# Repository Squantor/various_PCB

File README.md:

Various prototype PCB's
===========
This repository contains various little boards like level shifters, component breakouts and other simple PCB's. Most of these boards are breadboard plugin friendly and are available at OSH park.
<h1 align="center">Breakouts</h1>
Various breakout boards with additional supporting components to help the application
<h2 align="center">74HCT9046A PLL</h2>
Improved version of the venerable 47HC(T)4046 PLL, main improvement is fixing the deadtime problem with the Flipflop based phase detector and adding a bias resistor for the charge pump output.
<h2 align="center">GTL2003 level shifter</h2>
Bidirectional levelshifter working from 5V on one side to anything lower on the other. Pull up and biasing resistor pads/caps positions included.
<h2 align="center">GTL2003 current mirror/sink</h2>
The GTL2003 bidirectional levelshifter is nothing more then a bunch of N-MOSFETs on a single die with their gates interconnected. Due to close proximity of the FETs to eachother they (should) be reasonably matched well and the datasheet specifies this. Instead of using it for a level shifter application it could also be a multiple channel programmable current sink. Included on the board is a TL431 programmable zener reference with a bunch of resistor pads for biasing the mosfets with a stable voltage.
<h2 align="center">Filament transformer breakout</h2>
Breakout board for the Triad transformer 6.3V, used as a filament transformer for electrostatic CRT's. Going to be used for PM3210 oscilloscope repair.
<h1 align="center">Modules</h1>
<h2 align="center">Transformer module</h2>
Board with flexible transformer layout, bridge rectifier and smoothing caps. Multiple versions.

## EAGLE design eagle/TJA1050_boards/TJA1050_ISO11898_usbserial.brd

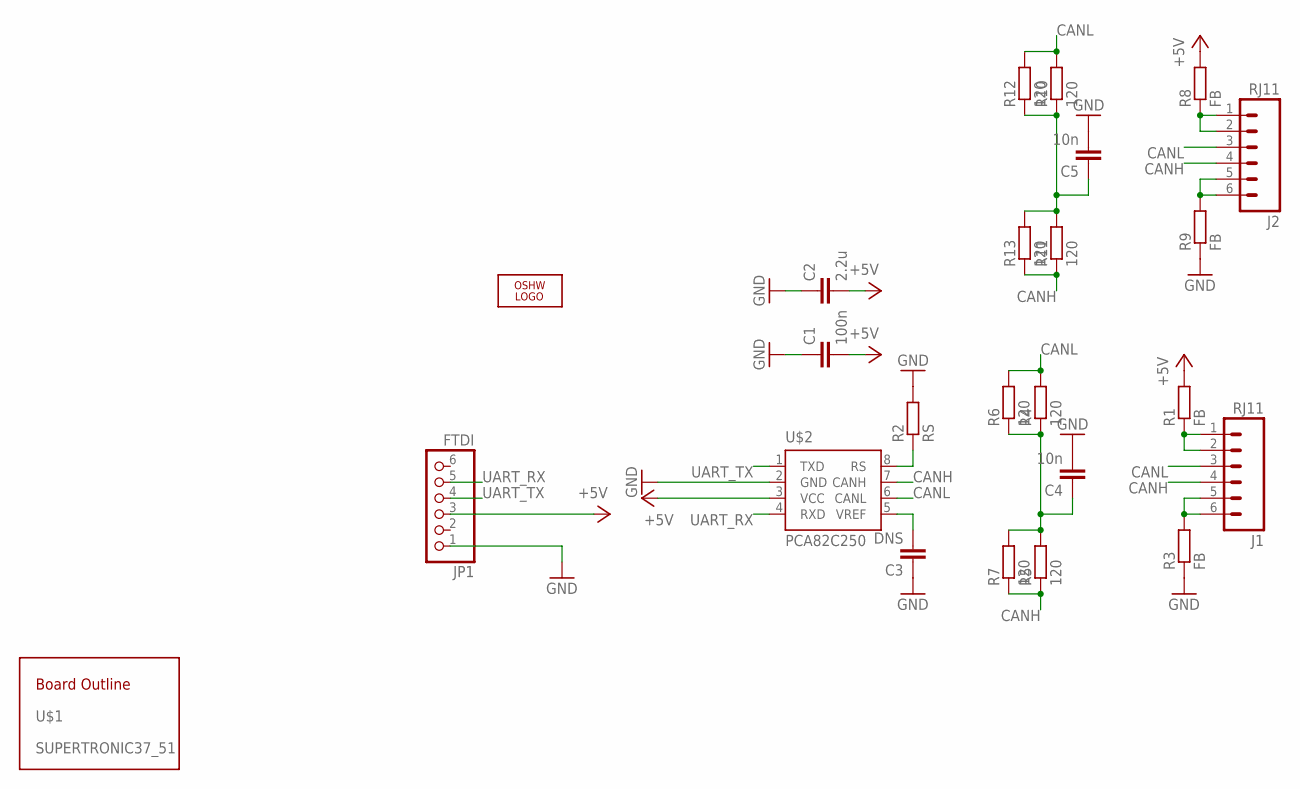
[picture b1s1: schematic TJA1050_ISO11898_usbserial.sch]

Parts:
C1: 100n; C0603
C2: 2.2u; C0805
C3: DNS; C0603
C4, C5: 10n; C0805
J1, J2: RJ11; RJ11-6
JP1: FTDI; 1X06
LOGO1: OSHW_LOGO_10MILX0200-NT; OSHW_10X200_NOTEXT
R1, R3, R8, R9: FB; R0805
R2: RS; R0603
R4, R5, R6, R7, R10, R11, R12, R13: 120; R0603
U$1: SUPERTRONIC37_51; SUPERTRONIC_37_51MM
U$2: PCA82C250; SOT96-1

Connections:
+5V: C1.2, C2.2, JP1.3, R1.2, R8.2, U$2.3 (VCC)
CANH: J1.4, J2.4, R5.1, R7.1, R11.1, R13.1, U$2.7 (CANH)
CANL: J1.3, J2.3, R4.2, R6.2, R10.2, R12.2, U$2.6 (CANL)
GND: C1.1, C2.1, C3.1, C4.2, C5.2, JP1.1, R2.2, R3.1, R9.1, U$2.2 (GND)
unnamed: J1.1, J1.2, R1.1
unnamed: C3.2, U$2.5 (VREF)
unnamed: J1.5, J1.6, R3.2
unnamed: C4.1, R4.1, R5.2, R6.1, R7.2
unnamed: R2.1, U$2.8 (RS)
unnamed: J2.1, J2.2, R8.1
unnamed: J2.5, J2.6, R9.2
unnamed: C5.1, R10.1, R11.2, R12.1, R13.2
UART_RX: JP1.5, U$2.4 (RXD)
UART_TX: JP1.4, U$2.1 (TXD)

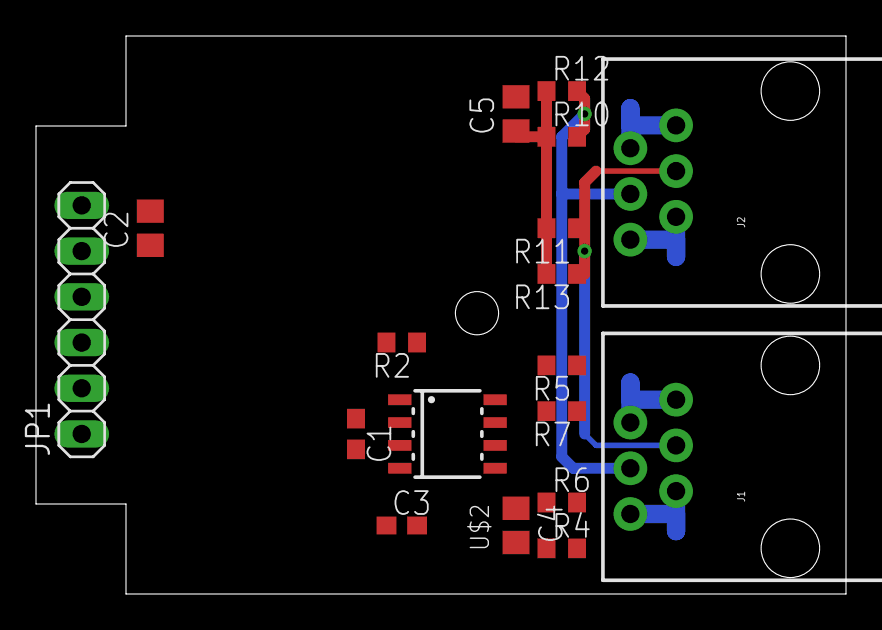
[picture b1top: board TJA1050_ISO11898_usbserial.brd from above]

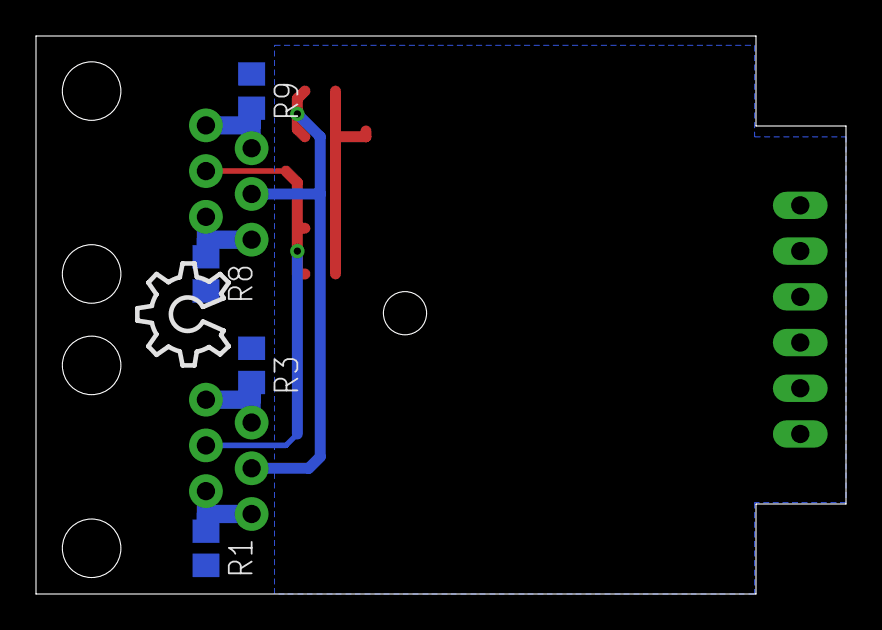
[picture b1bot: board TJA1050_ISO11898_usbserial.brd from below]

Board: 2 copper layers, 45.0 x 31.0 mm, 24 parts (5 on the bottom side), 14 nets.

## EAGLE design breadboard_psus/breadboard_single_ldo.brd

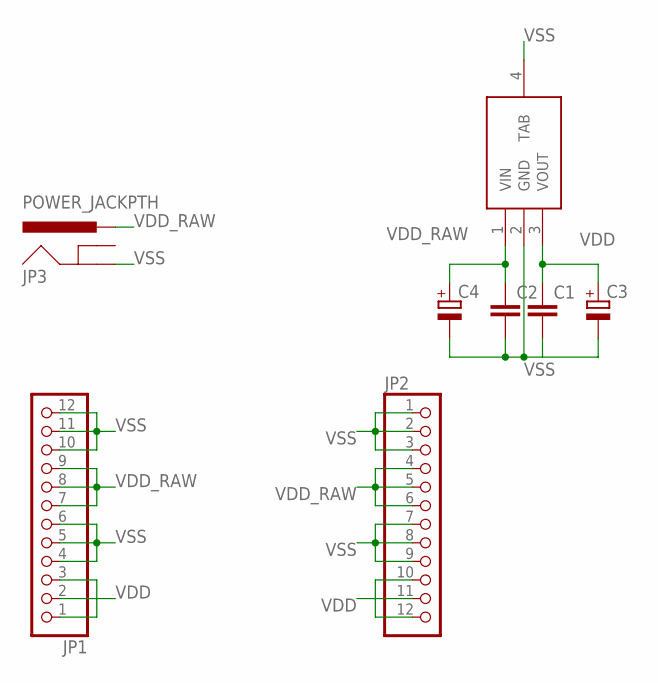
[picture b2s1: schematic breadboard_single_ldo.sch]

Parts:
C1, C2: C-EUC0805; C0805
C3, C4: CPOL-EUE3.5-8; E3,5-8
JP1, JP2: PINHD-1X12NORM_OCT; 1X12_NORMAL_OCT
JP3: POWER_JACKPTH; POWER_JACK_PTH
U$1: MCP1703T-3302E/DB; SOT223

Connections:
VDD: C1.1, C3.+, JP1.1, JP1.2, JP1.3, JP2.10, JP2.11, JP2.12, U$1.3 (VOUT)
VDD_RAW: C2.1, C4.+, JP1.7, JP1.8, JP1.9, JP2.4, JP2.5, JP2.6, JP3.PWR, U$1.1 (VIN)
VSS: C1.2, C2.2, C3.-, C4.-, JP1.4, JP1.5, JP1.6, JP1.10, JP1.11, JP1.12, JP2.1, JP2.2, JP2.3, JP2.7, JP2.8, JP2.9, JP3.GND, U$1.2 (GND), U$1.4 (TAB)

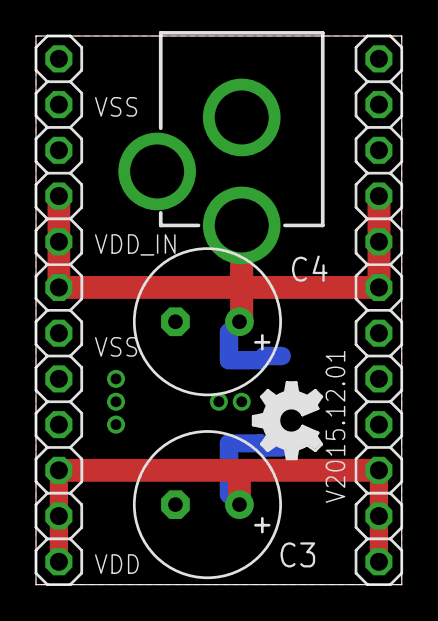
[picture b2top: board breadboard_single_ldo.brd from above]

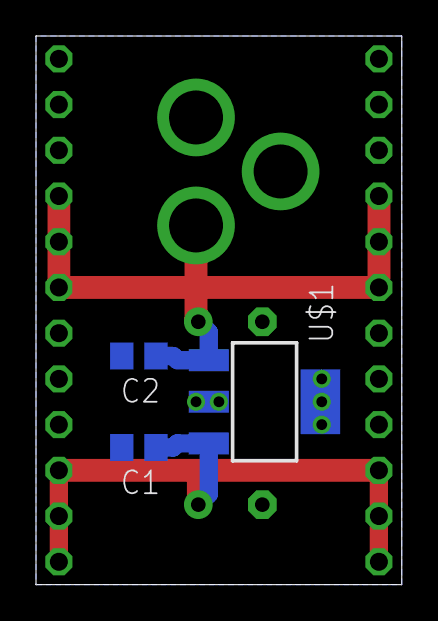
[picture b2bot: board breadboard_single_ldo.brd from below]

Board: 2 copper layers, 20.3 x 30.5 mm, 9 parts (3 on the bottom side), 3 nets.

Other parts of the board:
LOGO1: OSHW_LOGO_FILLX0150-NT; OSHW_FILLX150_NOTEXT

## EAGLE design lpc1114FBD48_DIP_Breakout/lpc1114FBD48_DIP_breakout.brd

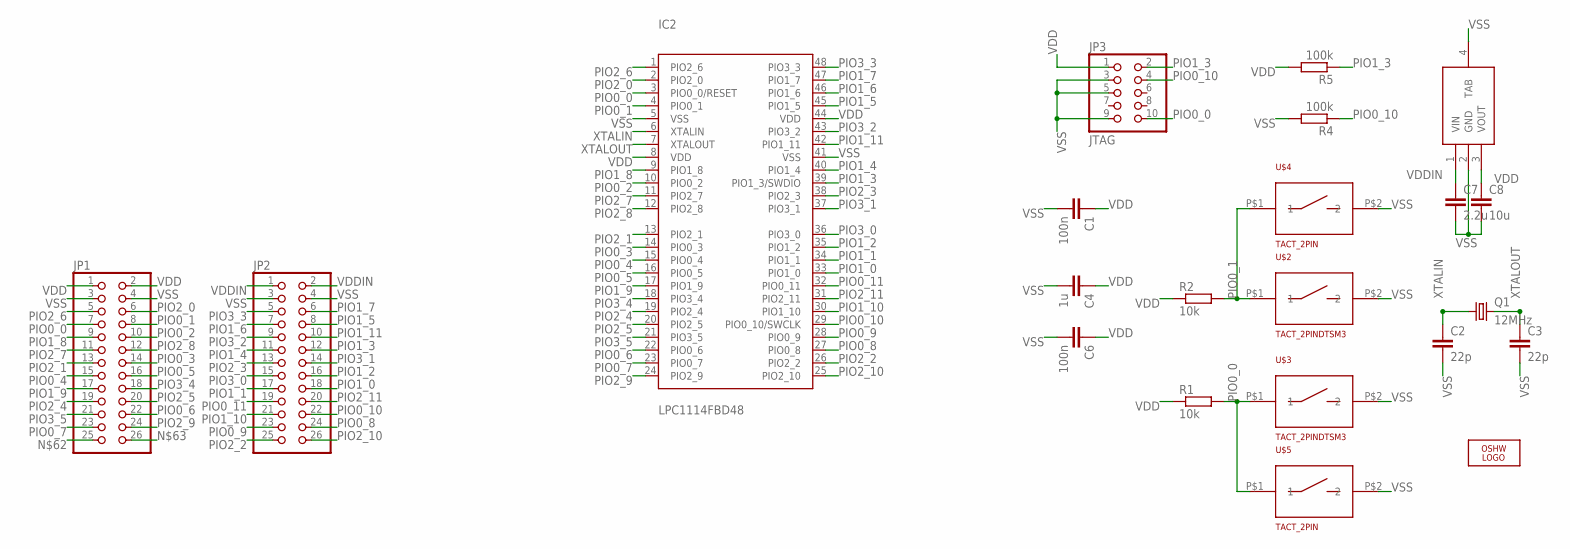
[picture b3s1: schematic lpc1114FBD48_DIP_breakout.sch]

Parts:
C1, C6: 100n; C0603K
C2, C3: 22p; C0603K
C4: 1u; C0805K
C7: 2.2u; C0805
C8: 10u; C0805
IC1: MCP1703T-3302E/DB; SOT223
IC2: LPC1114FBD48; SOT313-2
JP1, JP2: PINHD-2X13; 2X13
JP3: JTAG; 2X05_1.27_SMD
LOGO2: OSHW_LOGO_FILLX0150-NT; OSHW_FILLX150_NOTEXT
Q1: 12MHz; CRYSTAL_5.0X3.2
R1, R2: 10k; R0603
R4, R5: 100k; R0603
U$2, U$3: TACT_2PINDTSM3; DTSM3
U$4, U$5: TACT_2PIN; TD-85XU

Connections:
PIO0_0: IC2.3 (PIO0_0/RESET), JP1.7, JP3.10, R1.2, U$3.P$1 (1), U$5.P$1 (1)
PIO0_1: IC2.4 (PIO0_1), JP1.8, R2.2, U$2.P$1 (1), U$4.P$1 (1)
PIO0_2: IC2.10 (PIO0_2), JP1.10
PIO0_3: IC2.14 (PIO0_3), JP1.14
PIO0_4: IC2.15 (PIO0_4), JP1.15
PIO0_5: IC2.16 (PIO0_5), JP1.16
PIO0_6: IC2.22 (PIO0_6), JP1.22
PIO0_7: IC2.23 (PIO0_7), JP1.23
PIO0_8: IC2.27 (PIO0_8), JP2.24
PIO0_9: IC2.28 (PIO0_9), JP2.23
PIO0_10: IC2.29 (PIO0_10/SWCLK), JP2.22, JP3.4, R4.1
PIO0_11: IC2.32 (PIO0_11), JP2.19
PIO1_0: IC2.33 (PIO1_0), JP2.18
PIO1_1: IC2.34 (PIO1_1), JP2.17
PIO1_2: IC2.35 (PIO1_2), JP2.16
PIO1_3: IC2.39 (PIO1_3/SWDIO), JP2.12, JP3.2, R5.1
PIO1_4: IC2.40 (PIO1_4), JP2.11
PIO1_5: IC2.45 (PIO1_5), JP2.8
PIO1_6: IC2.46 (PIO1_6), JP2.7
PIO1_7: IC2.47 (PIO1_7), JP2.6
PIO1_8: IC2.9 (PIO1_8), JP1.9
PIO1_9: IC2.17 (PIO1_9), JP1.17
PIO1_10: IC2.30 (PIO1_10), JP2.21
PIO1_11: IC2.42 (PIO1_11), JP2.10
PIO2_0: IC2.2 (PIO2_0), JP1.6
PIO2_1: IC2.13 (PIO2_1), JP1.13
PIO2_2: IC2.26 (PIO2_2), JP2.25
PIO2_3: IC2.38 (PIO2_3), JP2.13
PIO2_4: IC2.19 (PIO2_4), JP1.19
PIO2_5: IC2.20 (PIO2_5), JP1.20
PIO2_6: IC2.1 (PIO2_6), JP1.5
PIO2_7: IC2.11 (PIO2_7), JP1.11
PIO2_8: IC2.12 (PIO2_8), JP1.12
PIO2_9: IC2.24 (PIO2_9), JP1.24
PIO2_10: IC2.25 (PIO2_10), JP2.26
PIO2_11: IC2.31 (PIO2_11), JP2.20
PIO3_0: IC2.36 (PIO3_0), JP2.15
PIO3_1: IC2.37 (PIO3_1), JP2.14
PIO3_2: IC2.43 (PIO3_2), JP2.9
PIO3_3: IC2.48 (PIO3_3), JP2.5
PIO3_4: IC2.18 (PIO3_4), JP1.18
PIO3_5: IC2.21 (PIO3_5), JP1.21
VDD: C1.1, C4.1, C6.1, C8.1, IC1.3 (VOUT), IC2.8 (VDD), IC2.44 (VDD), JP1.1, JP1.2, JP3.1, R1.1, R2.1, R5.2
VDDIN: C7.1, IC1.1 (VIN), JP2.1, JP2.2
VSS: C1.2, C2.2, C3.2, C4.2, C6.2, C7.2, C8.2, IC1.2 (GND), IC1.4 (TAB), IC2.5 (VSS), IC2.41 (VSS), JP1.3, JP1.4, JP2.3, JP2.4, JP3.3, JP3.5, JP3.9, R4.2, U$2.P$2 (2), U$3.P$2 (2), U$4.P$2 (2), U$5.P$2 (2)
XTALIN: C2.1, IC2.6 (XTALIN), Q1.1
XTALOUT: C3.1, IC2.7 (XTALOUT), Q1.2

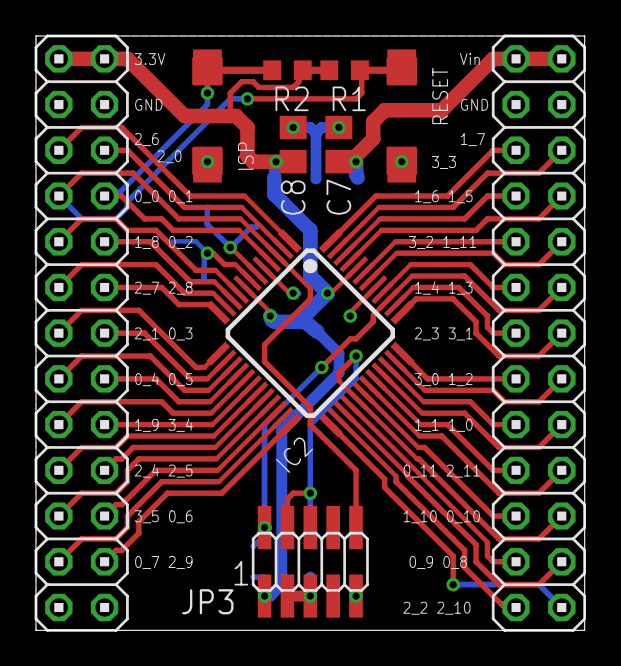
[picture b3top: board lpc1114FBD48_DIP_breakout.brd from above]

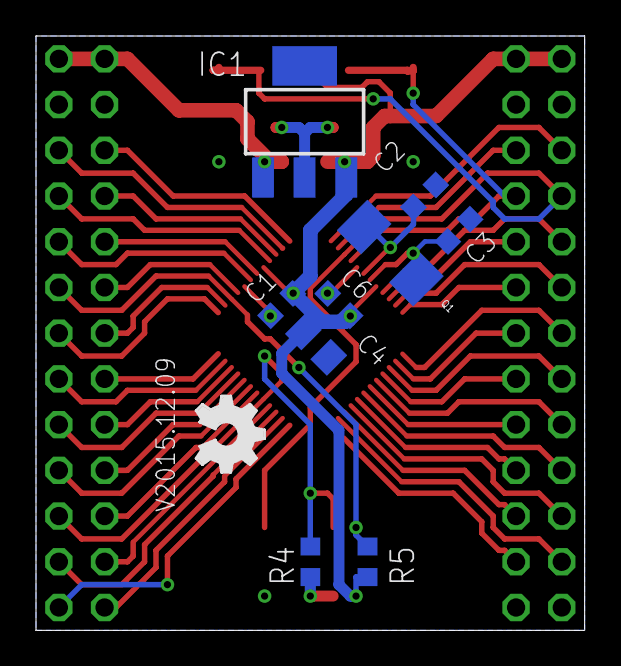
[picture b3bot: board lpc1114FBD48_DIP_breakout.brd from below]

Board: 2 copper layers, 30.5 x 33.0 mm, 22 parts (10 on the bottom side), 47 nets.

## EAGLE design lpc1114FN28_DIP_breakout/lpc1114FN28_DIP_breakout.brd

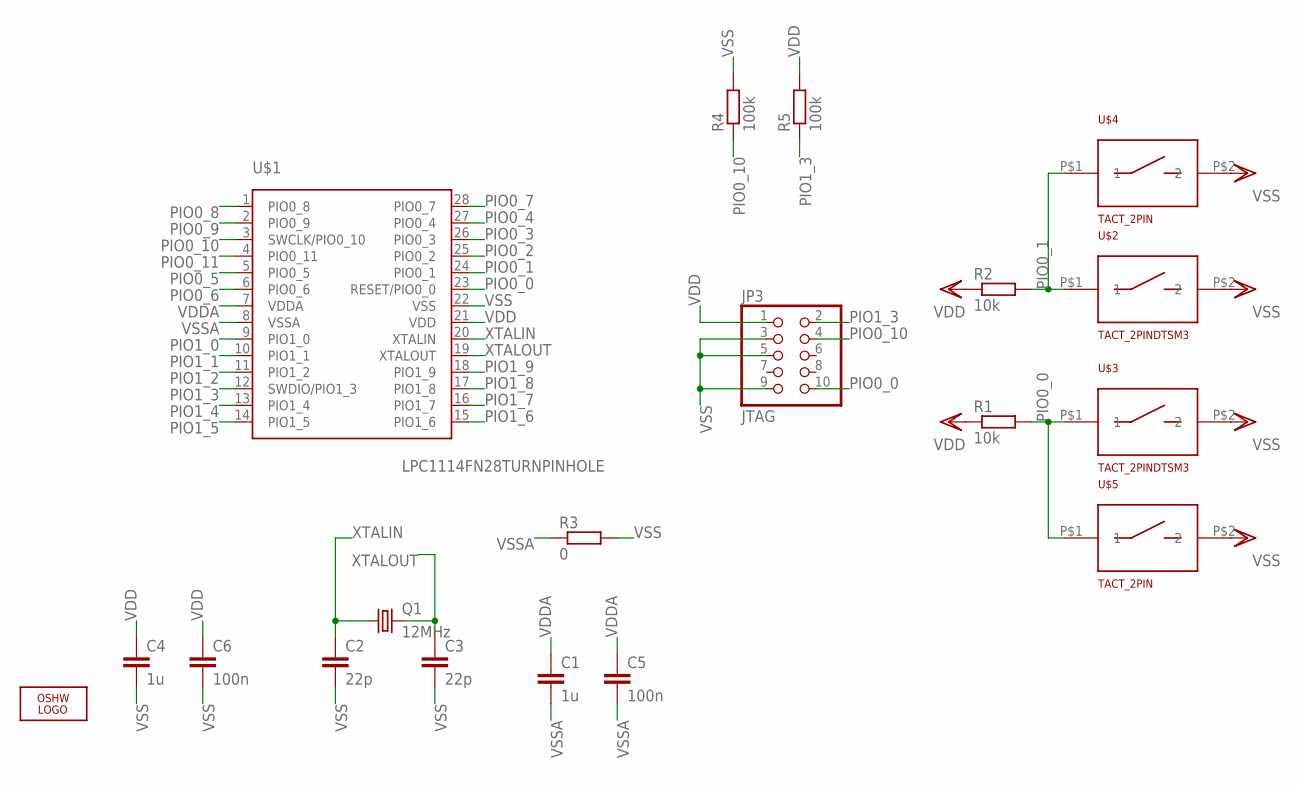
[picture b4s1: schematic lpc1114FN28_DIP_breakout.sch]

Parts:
C1, C4: 1u; C0805K
C2, C3: 22p; C0603K
C5, C6: 100n; C0603K
JP3: JTAG; 2X05_1.27_SMD
LOGO2: OSHW_LOGO_FILLX0150-NT; OSHW_FILLX150_NOTEXT
Q1: 12MHz; CRYSTAL_5.0X3.2
R1, R2: 10k; R0603
R3: 0; R0603
R4, R5: 100k; R0603
U$1: LPC1114FN28TURNPINHOLE; SOT117_TURNPINHOLE
U$2, U$3: TACT_2PINDTSM3; DTSM3
U$4, U$5: TACT_2PIN; TD-85XU

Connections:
PIO0_0: JP3.10, R1.2, U$1.23 (RESET/PIO0_0), U$3.P$1 (1), U$5.P$1 (1)
PIO0_1: R2.2, U$1.24 (PIO0_1), U$2.P$1 (1), U$4.P$1 (1)
PIO0_2: U$1.25 (PIO0_2)
PIO0_3: U$1.26 (PIO0_3)
PIO0_4: U$1.27 (PIO0_4)
PIO0_5: U$1.5 (PIO0_5)
PIO0_6: U$1.6 (PIO0_6)
PIO0_7: U$1.28 (PIO0_7)
PIO0_8: U$1.1 (PIO0_8)
PIO0_9: U$1.2 (PIO0_9)
PIO0_10: JP3.4, R4.1, U$1.3 (SWCLK/PIO0_10)
PIO0_11: U$1.4 (PIO0_11)
PIO1_0: U$1.9 (PIO1_0)
PIO1_1: U$1.10 (PIO1_1)
PIO1_2: U$1.11 (PIO1_2)
PIO1_3: JP3.2, R5.1, U$1.12 (SWDIO/PIO1_3)
PIO1_4: U$1.13 (PIO1_4)
PIO1_5: U$1.14 (PIO1_5)
PIO1_6: U$1.15 (PIO1_6)
PIO1_7: U$1.16 (PIO1_7)
PIO1_8: U$1.17 (PIO1_8)
PIO1_9: U$1.18 (PIO1_9)
VDD: C4.1, C6.1, JP3.1, R1.1, R2.1, R5.2, U$1.21 (VDD)
VDDA: C1.1, C5.1, U$1.7 (VDDA)
VSS: C2.2, C3.2, C4.2, C6.2, JP3.3, JP3.5, JP3.9, R3.2, R4.2, U$1.22 (VSS), U$2.P$2 (2), U$3.P$2 (2), U$4.P$2 (2), U$5.P$2 (2)
VSSA: C1.2, C5.2, R3.1, U$1.8 (VSSA)
XTALIN: C2.1, Q1.1, U$1.20 (XTALIN)
XTALOUT: C3.1, Q1.2, U$1.19 (XTALOUT)

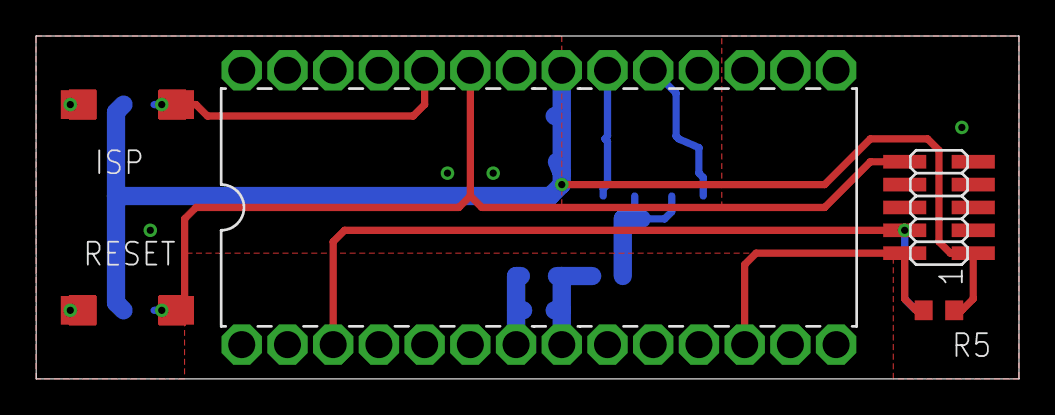
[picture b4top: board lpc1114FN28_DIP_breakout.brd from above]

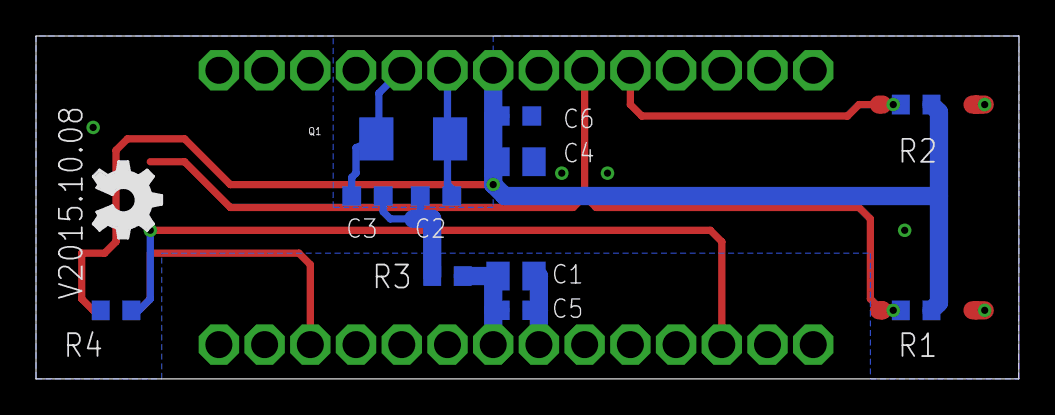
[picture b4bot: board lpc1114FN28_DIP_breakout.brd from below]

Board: 2 copper layers, 54.6 x 19.1 mm, 19 parts (12 on the bottom side), 10 nets.

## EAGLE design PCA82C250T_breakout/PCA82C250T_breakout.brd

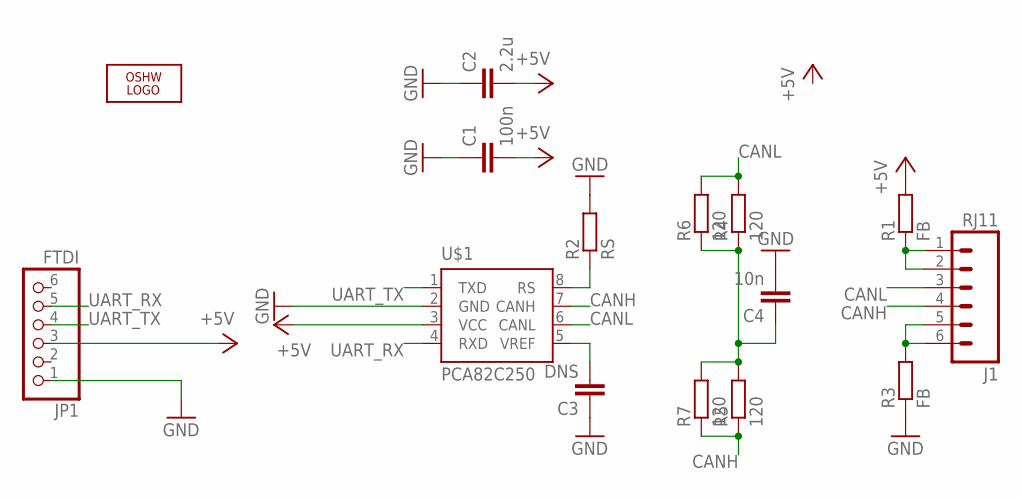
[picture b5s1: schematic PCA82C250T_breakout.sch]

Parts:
C1: 100n; C0603
C2: 2.2u; C0805
C3: DNS; C0603
C4: 10n; C0805
J1: RJ11; RJ11-6
JP1: FTDI; 1X06
LOGO1: OSHW_LOGO_10MILX0200-NT; OSHW_10X200_NOTEXT
R1, R3: FB; R0805
R2: RS; R0603
R4, R5, R6, R7: 120; R0603
U$1: PCA82C250; SOT96-1

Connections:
+5V: C1.2, C2.2, JP1.3, R1.2, U$1.3 (VCC)
CANH: J1.4, R5.1, R7.1, U$1.7 (CANH)
CANL: J1.3, R4.2, R6.2, U$1.6 (CANL)
GND: C1.1, C2.1, C3.1, C4.2, JP1.1, R2.2, R3.1, U$1.2 (GND)
unnamed: J1.1, J1.2, R1.1
unnamed: C3.2, U$1.5 (VREF)
unnamed: J1.5, J1.6, R3.2
unnamed: C4.1, R4.1, R5.2, R6.1, R7.2
unnamed: R2.1, U$1.8 (RS)
UART_RX: JP1.5, U$1.4 (RXD)
UART_TX: JP1.4, U$1.1 (TXD)

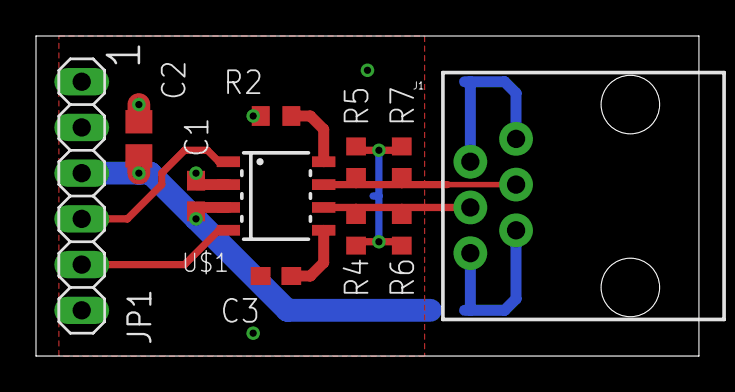
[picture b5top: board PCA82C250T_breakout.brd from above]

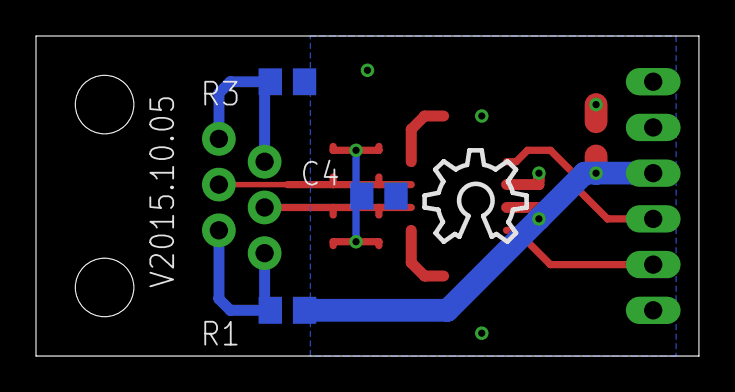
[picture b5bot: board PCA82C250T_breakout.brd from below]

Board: 2 copper layers, 36.8 x 17.8 mm, 15 parts (4 on the bottom side), 11 nets.

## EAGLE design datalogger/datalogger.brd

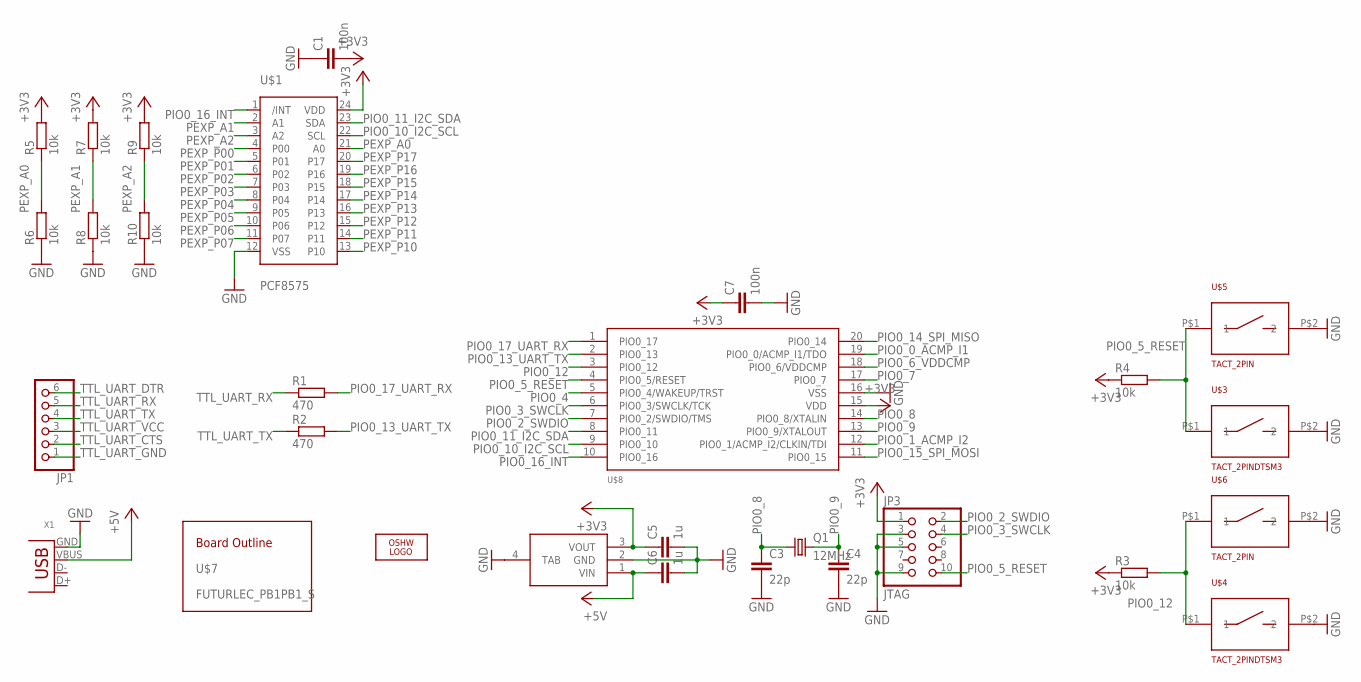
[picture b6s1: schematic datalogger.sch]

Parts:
C1, C7: 100n; C0603K
C3, C4: 22p; C0603K
C5, C6: 1u; C0805K
JP1: PINHD-1X6; 1X06
JP3: JTAG; 2X05_1.27_SMD
LOGO2: OSHW_LOGO_FILLX0150-NT; OSHW_FILLX150_NOTEXT
Q1: 12MHz; CRYSTAL_5.0X3.2
R1, R2: 470; R0603
R3, R4, R5, R6, R7, R8, R9, R10: 10k; R0603
U$1: PCF8575; SOT340
U$2: MCP1703T-3302E/DB; SOT223
U$3, U$4: TACT_2PINDTSM3; DTSM3
U$5, U$6: TACT_2PIN; TD-85XU
U$7: FUTURLEC_PB1PB1_S; FUTURLEC_PB1_SMALL
U$8: LPC812M101JDH20; TSSOP20
X1: USB-B-H

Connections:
+3V3: C1.2, C5.1, C7.1, JP3.1, R3.1, R4.1, R5.2, R7.2, R9.2, U$1.24 (VDD), U$2.3 (VOUT), U$8.15 (VDD)
+5V: C6.1, U$2.1 (VIN), X1.VBUS
GND: C1.1, C3.2, C4.2, C5.2, C6.2, C7.2, JP3.3, JP3.5, JP3.9, R6.1, R8.1, R10.1, U$1.12 (VSS), U$2.2 (GND), U$2.4 (TAB), U$3.P$2 (2), U$4.P$2 (2), U$5.P$2 (2), U$6.P$2 (2), U$8.16 (VSS), X1.GND
PEXP_A0: R5.1, R6.2, U$1.21 (A0)
PEXP_A1: R7.1, R8.2, U$1.2 (A1)
PEXP_A2: R9.1, R10.2, U$1.3 (A2)
PEXP_P00: U$1.4 (P00)
PEXP_P01: U$1.5 (P01)
PEXP_P02: U$1.6 (P02)
PEXP_P03: U$1.7 (P03)
PEXP_P04: U$1.8 (P04)
PEXP_P05: U$1.9 (P05)
PEXP_P06: U$1.10 (P06)
PEXP_P07: U$1.11 (P07)
PEXP_P10: U$1.13 (P10)
PEXP_P11: U$1.14 (P11)
PEXP_P12: U$1.15 (P12)
PEXP_P13: U$1.16 (P13)
PEXP_P14: U$1.17 (P14)
PEXP_P15: U$1.18 (P15)
PEXP_P16: U$1.19 (P16)
PEXP_P17: U$1.20 (P17)
PIO0_0_ACMP_I1: U$8.19 (PIO0_0/ACMP_I1/TDO)
PIO0_1_ACMP_I2: U$8.12 (PIO0_1/ACMP_I2/CLKIN/TDI)
PIO0_2_SWDIO: JP3.2, U$8.7 (PIO0_2/SWDIO/TMS)
PIO0_3_SWCLK: JP3.4, U$8.6 (PIO0_3/SWCLK/TCK)
PIO0_4: U$8.5 (PIO0_4/WAKEUP/TRST)
PIO0_5_RESET: JP3.10, R4.2, U$3.P$1 (1), U$5.P$1 (1), U$8.4 (PIO0_5/RESET)
PIO0_6_VDDCMP: U$8.18 (PIO0_6/VDDCMP)
PIO0_7: U$8.17 (PIO0_7)
PIO0_8: C3.1, Q1.1, U$8.14 (PIO0_8/XTALIN)
PIO0_9: C4.1, Q1.2, U$8.13 (PIO0_9/XTALOUT)
PIO0_10_I2C_SCL: U$1.22 (SCL), U$8.9 (PIO0_10)
PIO0_11_I2C_SDA: U$1.23 (SDA), U$8.8 (PIO0_11)
PIO0_12: R3.2, U$4.P$1 (1), U$6.P$1 (1), U$8.3 (PIO0_12)
PIO0_13_UART_TX: R2.2, U$8.2 (PIO0_13)
PIO0_14_SPI_MISO: U$8.20 (PIO0_14)
PIO0_15_SPI_MOSI: U$8.11 (PIO0_15)
PIO0_16_INT: U$1.1 (/INT), U$8.10 (PIO0_16)
PIO0_17_UART_RX: R1.2, U$8.1 (PIO0_17)
TTL_UART_CTS: JP1.2
TTL_UART_DTR: JP1.6
TTL_UART_GND: JP1.1
TTL_UART_RX: JP1.5, R1.1
TTL_UART_TX: JP1.4, R2.1
TTL_UART_VCC: JP1.3

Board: 2 copper layers, 29 parts (0 on the bottom side), 19 nets, no tracks yet.

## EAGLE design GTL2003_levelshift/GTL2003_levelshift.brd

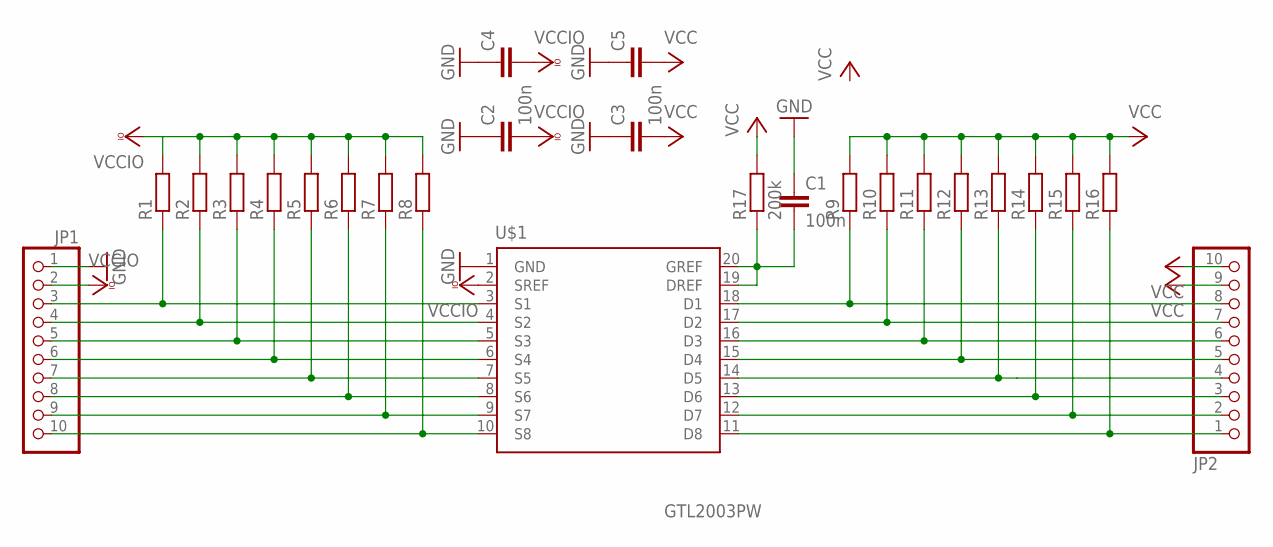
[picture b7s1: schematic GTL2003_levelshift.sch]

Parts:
C1, C2, C3: 100n; C0603
C4, C5: C-EUC0805; C0805
JP1, JP2: PINHD-1X10NORM_OCT; 1X10_NORMAL_OCT
R1, R2, R3, R4, R5, R6, R7, R8, R9, R10, R11, R12, R13, R14, R15, R16: R-EU_R0603; R0603
R17: 200k; R0603
U$1: GTL2003PW; SOT360

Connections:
GND: C1.1, C2.1, C3.1, C4.1, C5.1, JP1.1, U$1.1 (GND)
unnamed: JP1.3, R1.1, U$1.3 (S1)
unnamed: JP1.4, R2.1, U$1.4 (S2)
unnamed: JP1.5, R3.1, U$1.5 (S3)
unnamed: JP1.6, R4.1, U$1.6 (S4)
unnamed: JP1.7, R5.1, U$1.7 (S5)
unnamed: JP1.8, R6.1, U$1.8 (S6)
unnamed: JP1.9, R7.1, U$1.9 (S7)
unnamed: JP1.10, R8.1, U$1.10 (S8)
unnamed: JP2.8, R9.1, U$1.18 (D1)
unnamed: JP2.7, R10.1, U$1.17 (D2)
unnamed: JP2.6, R11.1, U$1.16 (D3)
unnamed: JP2.5, R12.1, U$1.15 (D4)
unnamed: JP2.4, R13.1, U$1.14 (D5)
unnamed: JP2.3, R14.1, U$1.13 (D6)
unnamed: JP2.2, R15.1, U$1.12 (D7)
unnamed: JP2.1, R16.1, U$1.11 (D8)
unnamed: C1.2, R17.1, U$1.19 (DREF), U$1.20 (GREF)
VCC: C3.2, C5.2, JP2.9, JP2.10, R9.2, R10.2, R11.2, R12.2, R13.2, R14.2, R15.2, R16.2, R17.2
VCCIO: C2.2, C4.2, JP1.2, R1.2, R2.2, R3.2, R4.2, R5.2, R6.2, R7.2, R8.2, U$1.2 (SREF)

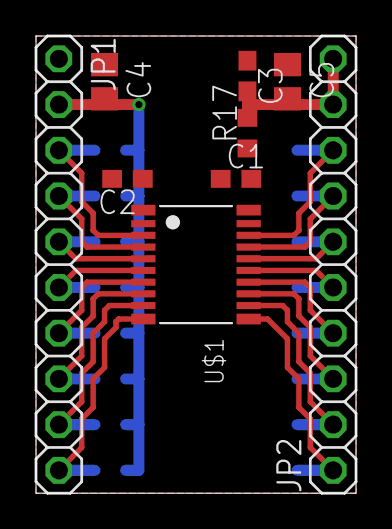
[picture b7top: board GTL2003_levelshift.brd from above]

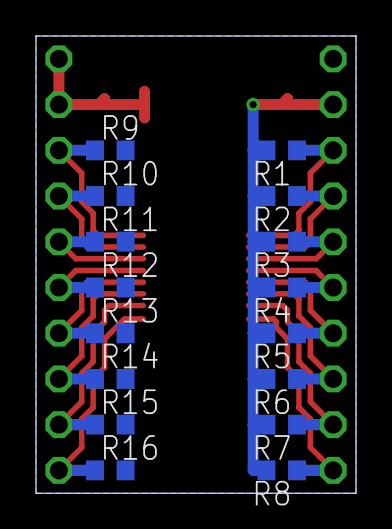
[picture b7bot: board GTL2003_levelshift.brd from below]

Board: 2 copper layers, 17.8 x 25.4 mm, 25 parts (16 on the bottom side), 20 nets.

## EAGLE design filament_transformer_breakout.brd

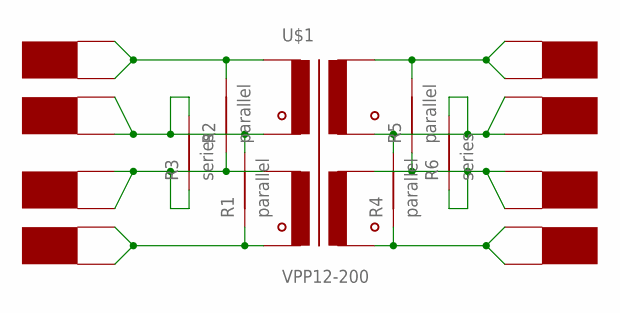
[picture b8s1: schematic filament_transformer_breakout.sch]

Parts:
R1, R2, R4, R5: parallel; 0309/12/BRIDGE
R3, R6: series; 0309/12/BRIDGE
U$1: VPP12-200; TRIADMAG1,5/8:1,5/16
U$2, U$3, U$4, U$5, U$6, U$7, U$8, U$9: FASTON_2PIN; FASTON_5.08

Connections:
unnamed: R1.2, R3.2, U$1.PRI1,2, U$3.1, U$3.2
unnamed: R1.1, U$1.PRI2,2, U$5.1, U$5.2
unnamed: R4.2, R6.2, U$1.SEC1,2, U$7.1, U$7.2
unnamed: R2.2, U$1.PRI1,1, U$2.1, U$2.2
unnamed: R2.1, R3.1, U$1.PRI2,1, U$4.1, U$4.2
unnamed: R4.1, U$1.SEC2,2, U$9.1, U$9.2
unnamed: R5.2, U$1.SEC1,1, U$6.1, U$6.2
unnamed: R5.1, R6.1, U$1.SEC2,1, U$8.1, U$8.2

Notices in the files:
parts and their libraries:
SparkFun-Connectors: Licensing: Creative Commons ShareAlike 4.0 International - https://creativecommons.org/licenses/by-sa/4.0
